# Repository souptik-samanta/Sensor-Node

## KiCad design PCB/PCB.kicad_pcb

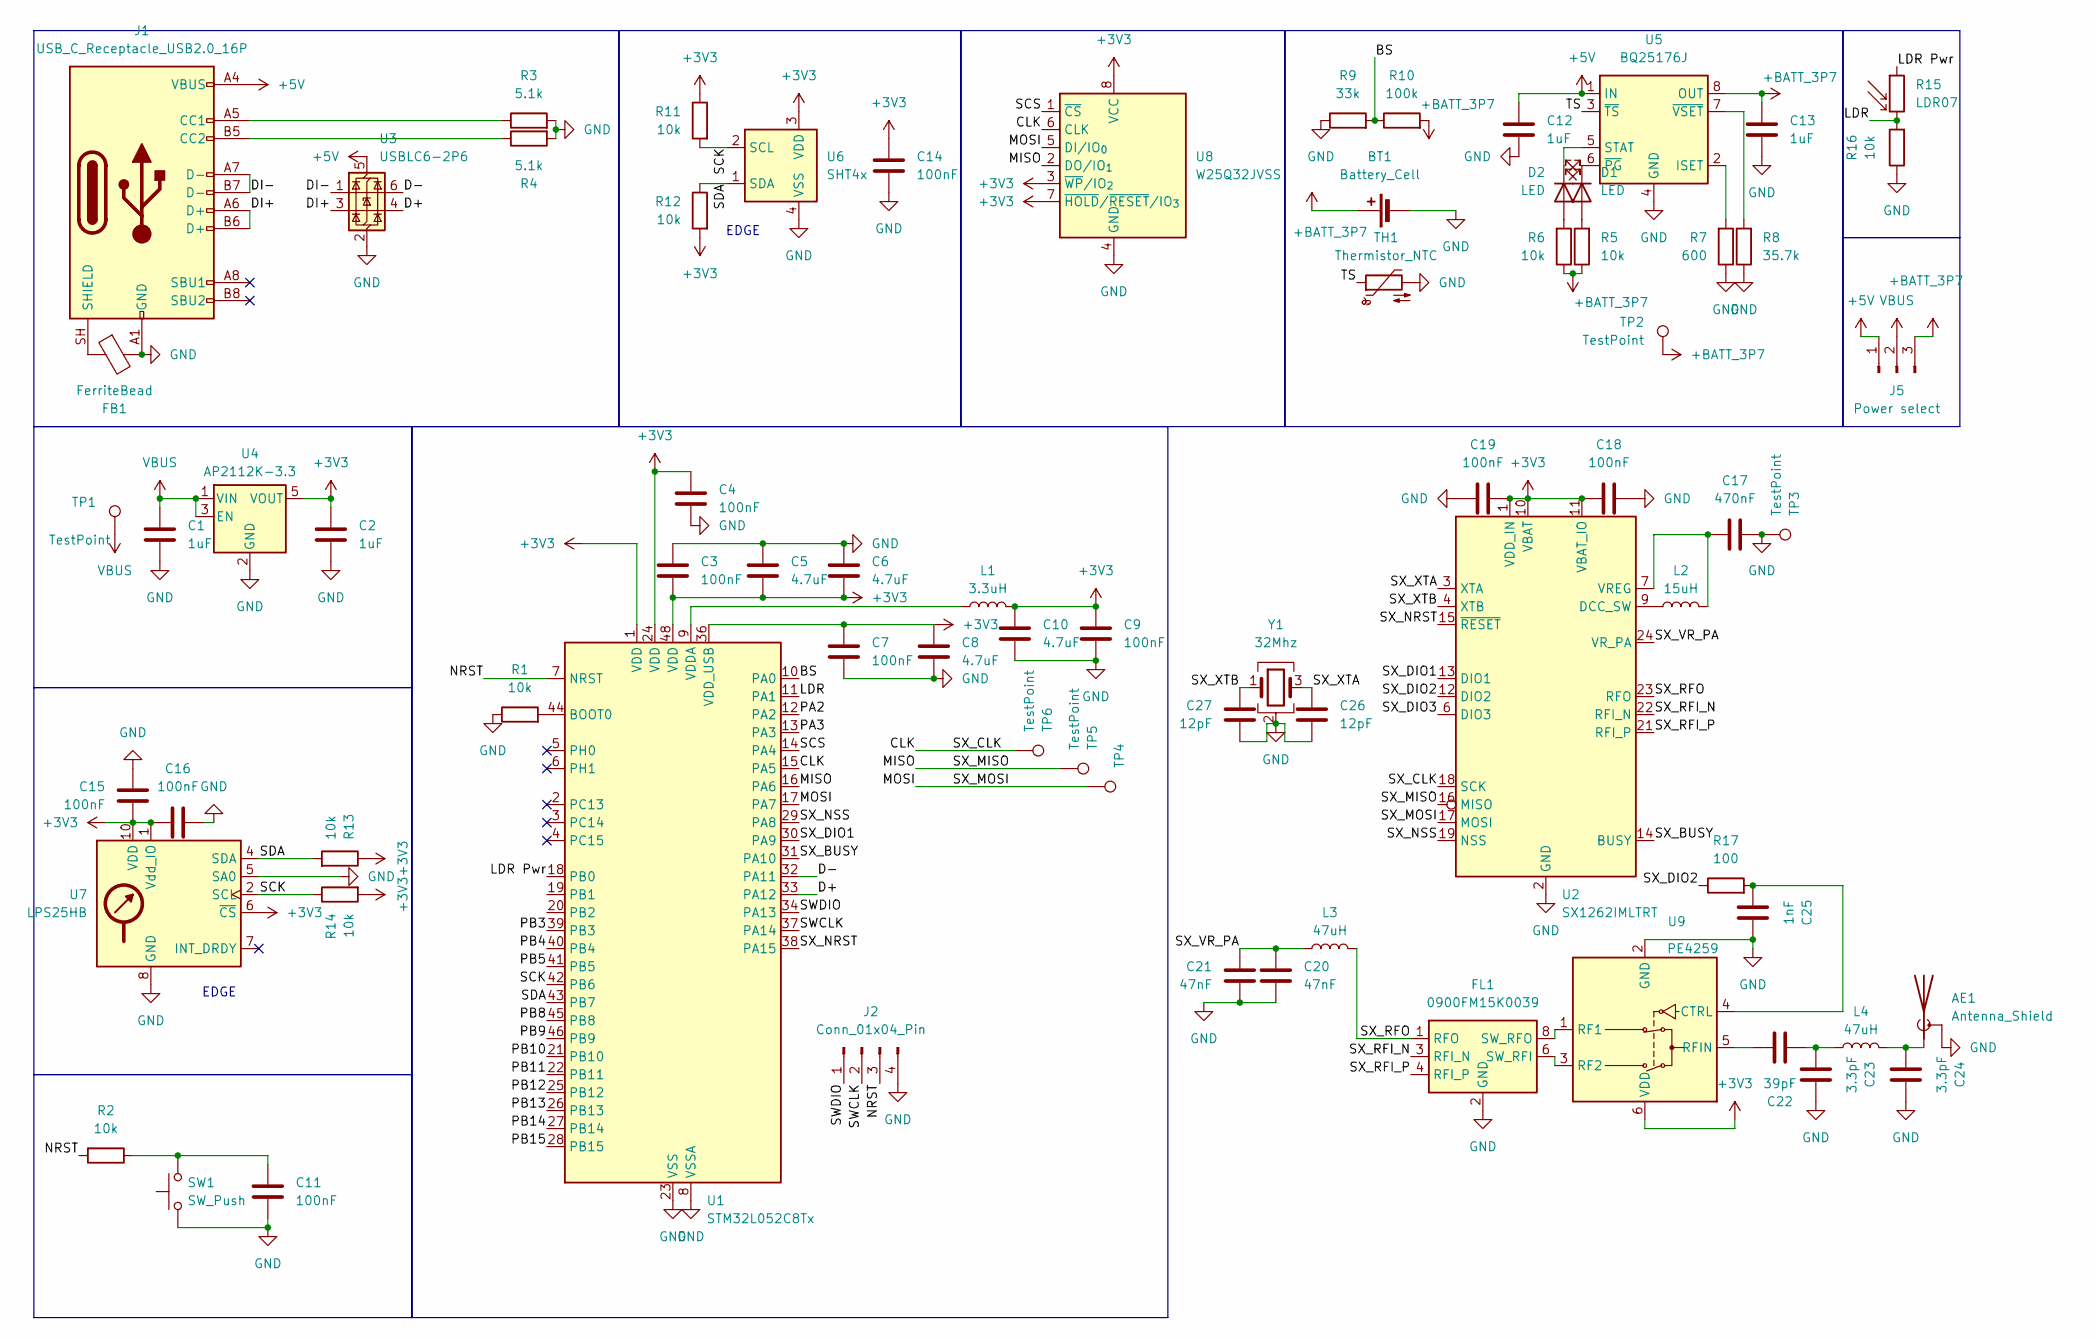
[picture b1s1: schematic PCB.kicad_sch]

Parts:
AE1: Antenna_Shield; SMA_Amphenol_901-144_Vertical
BT1: Battery_Cell; BatteryHolder_Keystone_1042_1x18650
C1, C2, C12, C13: 1uF; C_0402_1005Metric
C3, C4, C7, C9, C11, C14, C15, C16, C18, C19: 100nF; C_0402_1005Metric
C5, C6, C8, C10: 4.7uF; C_0402_1005Metric
C17: 470nF; C_0402_1005Metric
C20, C21: 47nF; C_0402_1005Metric
C22: 39pF; C_0402_1005Metric
C23, C24: 3.3pF; C_0402_1005Metric
C25: 1nF; C_0402_1005Metric
C26, C27: 12pF; C_0402_1005Metric
D1, D2: LED; LED_0402_1005Metric
FB1: FerriteBead; L_0402_1005Metric
FL1: 0900FM15K0039; Balun_Johanson_0900FM15K0039
J1: USB_C_Receptacle_USB2.0_16P; USB_C_Receptacle_GCT_USB4105-xx-A_16P_TopMnt_Horizontal
J2: Conn_01x04_Pin; PinHeader_1x04_P2.54mm_Vertical
J5: Power select; PinHeader_1x03_P2.54mm_Vertical
L1: 3.3uH; L_0402_1005Metric
L2: 15uH; L_0402_1005Metric
L3, L4: 47uH; L_0402_1005Metric
R1, R2, R5, R6, R11, R12, R13, R14, R16: 10k; R_0402_1005Metric
R3, R4: 5.1k; R_0402_1005Metric
R7: 600; R_0402_1005Metric
R8: 35.7k; R_0402_1005Metric
R9: 33k; R_0402_1005Metric
R10: 100k; R_0402_1005Metric
R15: LDR07; R_LDR_5.1x4.3mm_P3.4mm_Vertical
R17: 100; R_0402_1005Metric
SW1: SW_Push; SW_Push_SPST_NO_Alps_SKRK
TH1: Thermistor_NTC; R_Axial_DIN0204_L3.6mm_D1.6mm_P1.90mm_Vertical
TP1, TP2, TP3, TP4, TP5, TP6: TestPoint; TestPoint_Pad_D1.0mm
U1: STM32L052C8Tx; LQFP-48_7x7mm_P0.5mm
U2: SX1262IMLTRT; QFN-24-1EP_4x4mm_P0.5mm_EP2.7x2.7mm
U3: USBLC6-2P6; SOT-666
U4: AP2112K-3.3; SOT-23-5
U5: BQ25176J; WSON-8-1EP_2x2mm_P0.5mm_EP0.9x1.6mm
U6: SHT4x; Sensirion_DFN-4_1.5x1.5mm_P0.8mm_SHT4x_NoCentralPad
U7: LPS25HB; ST_HLGA-10_2.5x2.5mm_P0.6mm_LayoutBorder3x2y
U8: W25Q32JVSS; SOIC-8_5.3x5.3mm_P1.27mm
U9: PE4259; SOT-363_SC-70-6
Y1: 32Mhz; Crystal_SMD_3225-4Pin_3.2x2.5mm

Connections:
+3V3: C2.1, C3.2, C4.1, C5.2, C6.2, C9.1, C10.2, C14.1, C15.2, C16.2, C18.1, C19.2, L1.2, R11.1, R12.2, R13.1, R14.2, U1.1 (VDD), U1.24 (VDD), U1.48 (VDD), U2.1 (VDD_IN), U2.10 (VBAT), U2.11 (VBAT_IO), U4.5 (VOUT), U6.3 (VDD), U7.1 (Vdd_IO), U7.6 (~CS), U7.10 (VDD), U8.3 (~WP/IO_{2}), U8.7 (~HOLD/~RESET/IO_{3}), U8.8 (VCC), U9.6 (VDD)
+5V: C12.2, J1.A4 (VBUS), J1.A9 (VBUS), J1.B4 (VBUS), J1.B9 (VBUS), J5.1, U3.5 (VBUS), U5.1 (IN)
+BATT_3P7: BT1.1 (+), C13.2, J5.3, R5.1, R6.1, R10.2, TP2.1 (1_1), U5.8 (OUT)
/BS: R9.2, R10.1, U1.10 (PA0)
/CLK: TP6.1 (1_1), U1.15 (PA5), U2.18 (SCK), U8.6 (CLK)
/D+: U1.33 (PA12), U3.4 (I/O2)
/D-: U1.32 (PA11), U3.6 (I/O1)
/DI+: J1.A6 (D+), J1.B6 (D+), U3.3 (I/O2)
/DI-: J1.A7 (D-), J1.B7 (D-), U3.1 (I/O1)
/LDR: R15.2, R16.2, U1.11 (PA1)
/LDR Pwr: R15.1, U1.18 (PB0)
/MISO: TP5.1 (1_1), U1.16 (PA6), U2.16 (MISO), U8.2 (DO/IO_{1})
/MOSI: TP4.1 (1_1), U1.17 (PA7), U2.17 (MOSI), U8.5 (DI/IO_{0})
/NRST: J2.3, R2.2, U1.7 (NRST)
/PA2: U1.12 (PA2)
/PA3: U1.13 (PA3)
/PB3: U1.39 (PB3)
/PB4: U1.40 (PB4)
/PB5: U1.41 (PB5)
/PB8: U1.45 (PB8)
/PB9: U1.46 (PB9)
/PB10: U1.21 (PB10)
/PB11: U1.22 (PB11)
/PB12: U1.25 (PB12)
/PB13: U1.26 (PB13)
/PB14: U1.27 (PB14)
/PB15: U1.28 (PB15)
/SCK: R11.2, R14.1, U1.42 (PB6), U6.2 (SCL), U7.2 (SCL)
/SCS: U1.14 (PA4), U8.1 (~CS)
/SDA: R12.1, R13.2, U1.43 (PB7), U6.1 (SDA), U7.4 (SDA)
/SWCLK: J2.2, U1.37 (PA14)
/SWDIO: J2.1, U1.34 (PA13)
/SX_BUSY: U1.31 (PA10), U2.14 (BUSY)
/SX_DIO1: U1.30 (PA9), U2.13 (DIO1)
/SX_DIO2: R17.1, U2.12 (DIO2)
/SX_DIO3: U2.6 (DIO3)
/SX_NRST: U1.38 (PA15), U2.15 (~RESET)
/SX_NSS: U1.29 (PA8), U2.19 (NSS)
/SX_RFI_N: FL1.3 (RFI_N), U2.22 (RFI_N)
/SX_RFI_P: FL1.4 (RFI_P), U2.21 (RFI_P)
/SX_RFO: FL1.1 (RFO), L3.2, U2.23 (RFO)
/SX_VR_PA: C20.2, C21.2, L3.1, U2.24 (VR_PA)
/SX_XTA: C26.2, U2.3 (XTA), Y1.3
/SX_XTB: C27.2, U2.4 (XTB), Y1.1
/TS: TH1.1, U5.3 (~TS)
GND: AE1.2 (Shield), BT1.2 (-), C1.2, C2.2, C3.1, C4.2, C5.1, C6.1, C7.2, C8.2, C9.2, C10.1, C11.1, C12.1, C13.1, C14.2, C15.1, C16.1, C17.2, C18.2, C19.1, C20.1, C21.1, C23.2, C24.2, C25.2, C26.1, C27.1, FB1.2, FL1.2 (GND), FL1.5 (GND), FL1.7 (GND), FL1.9 (GND), FL1.10 (GND), J1.A1 (GND), J1.A12 (GND), J1.B1 (GND), J1.B12 (GND), J2.4, R1.1, R3.2, R4.2, R7.1, R8.1, R9.1, R16.1, SW1.1, TH1.2, TP3.1 (1_1), U1.8 (VSSA), U1.23 (VSS), U1.35 (VSS), U1.47 (VSS), U2.2 (GND), U2.5 (GND), U2.8 (GND), U2.20 (GND), U2.25 (GND), U3.2 (GND), U4.2 (GND), U5.4 (GND), U5.9 (GND), U6.4 (VSS), U7.3 (GND), U7.5 (SA0), U7.8 (GND), U7.9 (GND), U8.4 (GND), U9.2 (GND), Y1.2 (G), Y1.4 (G)
unnamed: AE1.1 (A), C24.1, L4.2
unnamed: C11.2, R2.1, SW1.2
unnamed: C22.1, C23.1, L4.1
unnamed: D1.2 (A), R5.2
unnamed: D1.1 (K), U5.6 (~PG)
unnamed: D2.2 (A), R6.2
unnamed: D2.1 (K), U5.5 (STAT)
unnamed: FL1.6 (SW_RFI), U9.3 (RF2)
unnamed: FL1.8 (SW_RFO), U9.1 (RF1)
unnamed: J1.A5 (CC1), R3.1
unnamed: J1.B5 (CC2), R4.1
unnamed: FB1.1, J1.SH (SHIELD)
unnamed: R1.2, U1.44 (BOOT0)
unnamed: L1.1, U1.9 (VDDA)
unnamed: C7.1, C8.1, U1.36 (VDD_USB)
unnamed: L2.1, U2.9 (DCC_SW)
unnamed: C17.1, L2.2, U2.7 (VREG)
unnamed: R7.2, U5.2 (ISET)
unnamed: R8.2, U5.7 (~VSET)
unnamed: C25.1, R17.2, U9.4 (CTRL)
unnamed: C22.2, U9.5 (RFIN)
VBUS: C1.1, J5.2, TP1.1 (1_1), U4.1 (VIN), U4.3 (EN)

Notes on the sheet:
EDGE

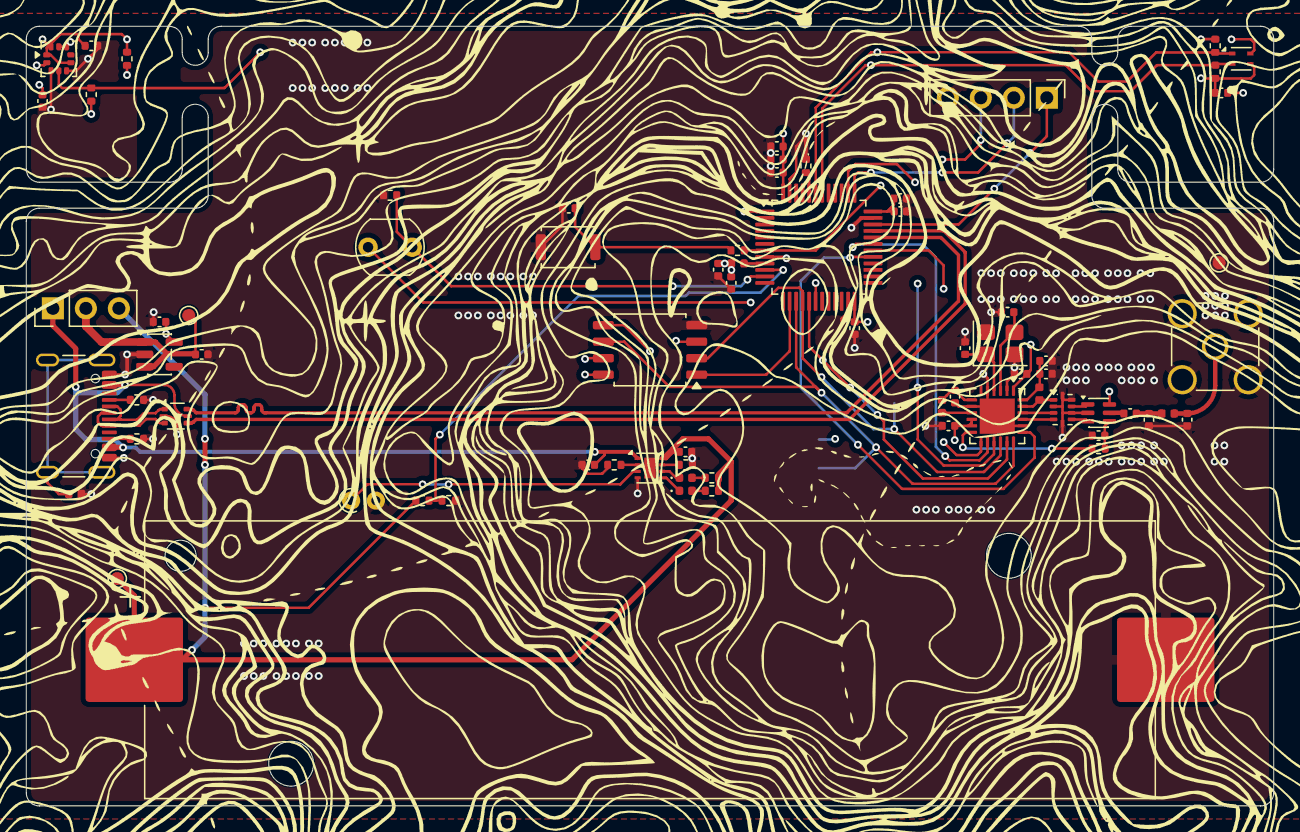
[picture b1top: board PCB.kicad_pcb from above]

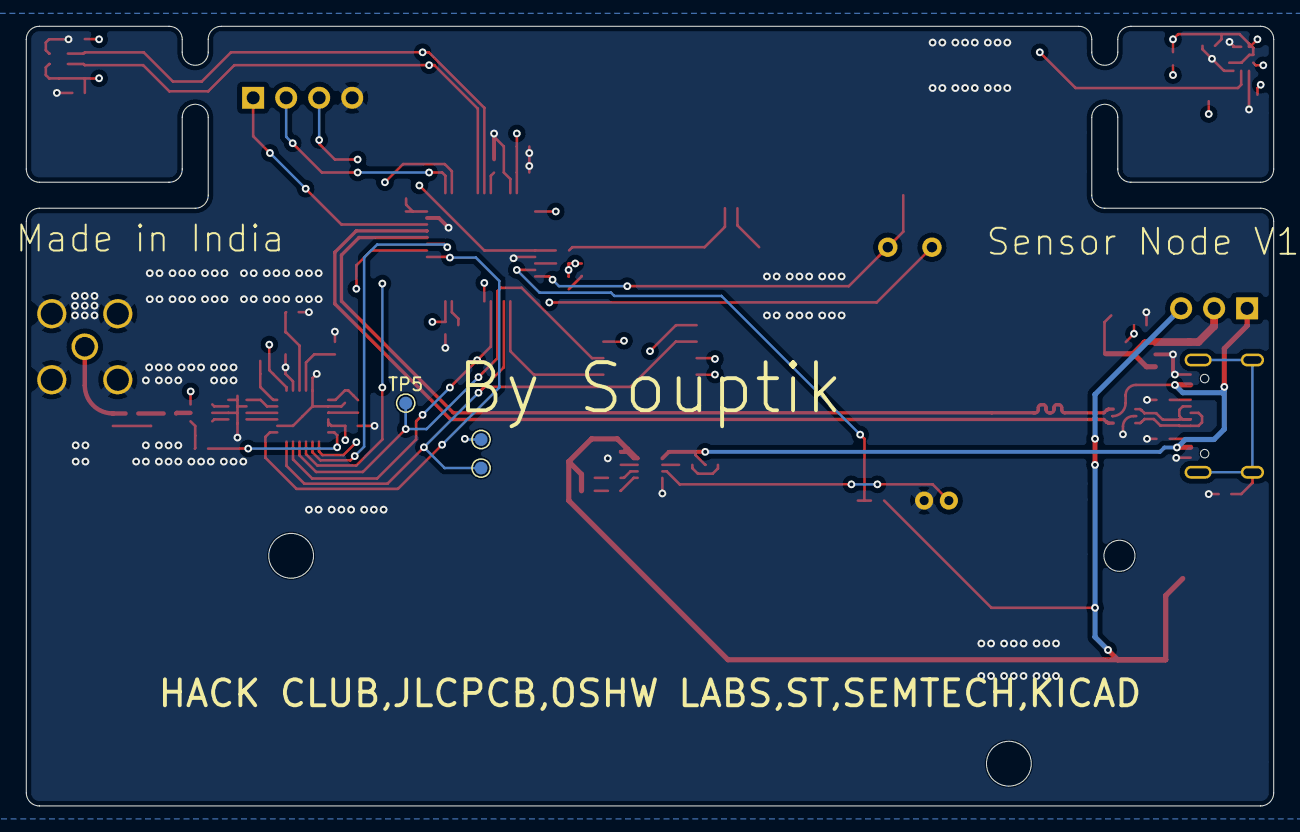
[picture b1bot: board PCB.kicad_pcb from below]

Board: 4 copper layers, 96.0 x 60.0 mm, 75 parts (3 on the bottom side), 54 nets.

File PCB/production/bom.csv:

Designator,Footprint,Quantity,Value,LCSC Part #
AE1,SMA_Amphenol_901-144_Vertical,1,Antenna_Shield,
BT1,BatteryHolder_Keystone_1042_1x18650,1,Battery_Cell,
"C1, C12, C13, C2",0402,4,1uF,
"C10, C5, C6, C8",0402,4,4.7uF,
"C11, C14, C15, C16, C18, C19, C3, C4, C7, C9",0402,10,100nF,
C17,0402,1,470nF,
"C20, C21",0402,2,47nF,
C22,0402,1,39pF,
"C23, C24",0402,2,3.3pF,
C25,0402,1,1nF,
"C26, C27",0402,2,12pF,
"D1, D2",0402,2,LED,
FB1,0402,1,FerriteBead,
FL1,Balun_Johanson_0900FM15K0039,1,0900FM15K0039,
J1,USB_C_Receptacle_GCT_USB4105-xx-A_16P_TopMnt_Horizontal,1,USB_C_Receptacle_USB2.0_16P,
J2,PinHeader_1x04_P2.54mm_Vertical,1,Conn_01x04_Pin,
J5,PinHeader_1x03_P2.54mm_Vertical,1,Power select,
L1,0402,1,3.3uH,
L2,0402,1,15uH,
"L3, L4",0402,2,47uH,
"R1, R11, R12, R13, R14, R16, R2, R5, R6",0402,9,10k,
R10,0402,1,100k,
R15,R_LDR_5.1x4.3mm_P3.4mm_Vertical,1,LDR07,
R17,0402,1,100,
"R3, R4",0402,2,5.1k,
R7,0402,1,600,
R8,0402,1,35.7k,
R9,0402,1,33k,
SW1,SW_Push_SPST_NO_Alps_SKRK,1,SW_Push,
TH1,R_Axial_DIN0204_L3.6mm_D1.6mm_P1.90mm_Vertical,1,Thermistor_NTC,
"TP1, TP2, TP3, TP4, TP5, TP6",TestPoint_Pad_D1.0mm,6,TestPoint,
U1,LQFP-48_7x7mm_P0.5mm,1,STM32L052C8Tx,
U2,QFN-24-1EP_4x4mm_P0.5mm_EP2.7x2.7mm,1,SX1262IMLTRT,
U3,SOT-666,1,USBLC6-2P6,
U4,SOT-23-5,1,AP2112K-3.3,
U5,WSON-8-1EP_2x2mm_P0.5mm_EP0.9x1.6mm,1,BQ25176J,
U6,Sensirion_DFN-4_1.5x1.5mm_P0.8mm_SHT4x_NoCentralPad,1,SHT4x,
U7,ST_HLGA-10_2.5x2.5mm_P0.6mm_LayoutBorder3x2y,1,LPS25HB,
U8,SOIC-8_5.3x5.3mm_P1.27mm,1,W25Q32JVSS,
U9,SOT-363_SC-70-6,1,PE4259,
Y1,Crystal_SMD_3225-4Pin_3.2x2.5mm,1,32Mhz,

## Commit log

2026-06-28 PCB MOSTLY DONE
